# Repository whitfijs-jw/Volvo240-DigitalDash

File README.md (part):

# DigitalDash

Volvo 240 Digital Dash Project.  Designed to use existing dash connectors (circular connectors w/ 2mm pins, vehicle speed sensor (VSS) connector, and various spade connectors) to
minimize extra wiring effort and installation of superfluous sensors.

## Features
### Plug and play with stock sensors and dash connectors
One of the main goals of the project was to use the existing Volvo 240 connectors. The only additional connectors and wiring needed are for sensors that weren't available on the stock main dash (oil pressure, oil temperature, vacuum/boost pressure, etc). Dash lights (low oil pressure, battery voltage, parking brake,high beams, etc) are functional as well as turn indicators. Fuel level and coolant temperature are functional.
The hardware supports the addition of common accessory sensors such as oil pressure, oil temperature, manifold absolute pressure, and ambient temperature.

### Multiple dash styles
Different Volvo dash styles can be displayed:
#### 240 w/ Tach

#### 240 w/ Clock

#### R-Sport Style

#### P1800 Style

#### 850R

#### 740/940 Style

#### 544/140 Linear Style

#### Early 240 Style

#### 140 Rallye Style

#### 240 Style Custom Layouts

### Accessory Gauges
The raspberry pi 4 supports 2 HDMI outputs so a second screen can be added where normal 52mm accessory gauges would have been placed:

Touch screen controls on this screen can be used to changed between dash layouts and also to reset trip odometers.  The style of the accessory gauges reflects the style of the main dash layout.

## Project Structure:
### /QtDash

This directory contains the hardware and software components that makeup the dash. There are also various visual/graphical assets that are used in the dash app.

#### /QtDash/VolvoDigitalDashModels

This directory contains the Qt app and related unit tests.  It is advised to use [QtCreator](https://www.qt.io/product/development-tools) to edit and compile the app. Using QtCreator to `QtDash/VolvoDigitalDashModels/subdirs.pro` will load both the app and the unit tests. The app is written using C/C++ for interfacing with the various sensors and QML for the UI.

#### /QtDash/Hardware

This directory contains the hardware that has been designed for this project.  Most of the PCBs have been designed using Eagle 7.7 as this is what I am most familiar with. The future of Eagle is questionable as an open source/free tool, so Kicad 6 will be used more and more as I become more familiar with it.

##### /QtDash/Hardware/DashHat

This directory contains the schematics and board files for the PCB that directly interfaces with the Raspberry Pi 40 pin header.  The board is split up into a low voltage (3.3/5V) that is powered from the Pi header and a high voltage (car battery voltage 8-16V) that is powered from the 240 ignition switch via the VSS connector.  The high voltage side is optically isolated from the low voltage side using optoislators.

##### /QtDash/Hardware/Cold Start Power Supply

This directory contains the schematics and board files for the cold start tolerant power supply design based around the LM3488. The input range is ~3V-24V and the output is ~5V rated at 3A.  During bench testing the input power needs to be above 5V when first powering up, and then could drop to ~3V while still continuously powering the Pi. This is a little overkill as the battery voltage during cranking only momentarily drops to 3V-4V before recovering very quickly to >10V.

##### /QtDash/Hardware/Screen Mounting

This directory contains the `.stl` files for mounting the HSD123KPW2-D10 12.3" TFT LCD using the stock 240 dash mounting holes.  These mounts will put the screen flush with the surrounding dash. The mounts and all other 3D modeling/CAD has been done using [Onshape](https://cad.onshape.com/documents/a41976d465f773bfdcbe5a50/w/2aee2fa256d8f08e0c531410/e/f563da56c6a88e94f86205e9). Included in the public OnShape document are models of the main PCB, HSD123KPW2-D10 LCD, screen mounts, etc.

##### /QtDash/Hardware/Simulation

This directory contains SPICE simulations of various circuits used in the dash. This is more of a scratchpad than it is a serious attempt at accurate real-life simulations.

##### /QtDash/Hardware/TachAdapter

This directory contains the schematics and board files for the tach signal adapter.  This board takes the high voltage pulses (>30V on my 88 245) and converts them to a square wave that can be used by the dash software to calculate RPM. The high voltage pulses are optically isolated from the dash/pi side to prevent any unwanted noise or damage to the pi or other hardware.

##### /QtDash/Hardware/VSS Adapter

This directory contains the schematics and board files for the VSS signal adapter. This board is based on the MAX9924 VR signal conditioning IC and takes the VR signal from the stock Volvo differential cover sensor and converts it into a square wave to be used by the dash software to calculated speed.

### /buildroot

This directory contains Buildroot, a tool used to generate a custom embedded Linux system that runs on the Pi. Buildroot allows us to generate a stripped down Linux system that has just enough to get the dash running.  This is the directory where you'll need to be to start linux image builds.

Below are relevant directories for this project within the buildroot directory structure:

#### /buildroot/board/volvodash

This directory contains the rootfs overlay for the dash as well as the custom scripts and configurations used whilst building the dash linux image. 

#### /buildroot/configs

This directory contains the configuration files for various boards. The relevant files for this project are `volvodash_defconfig` and `volvodash_rpi4_defconfig`.

#### /buildroot/output/images

This directory contains the outputs of the buildroot compilation process. After buildroot is done compiling the custom linux image, compiling the specified target packages, and constructing the target rootfs and bootfs, an image that can be flashed on to an SD card is placed here.  `sdcard.img` can then be flashed on to an SD card to be used on a pi.  As a part of the compilation/building the Qt Dash app should be compiled and placed within this image.  For more detailed information see *Setting Up Buildroot* below.

## Project components:
- Raspberry Pi 3 or Raspberry Pi 4/400
- 12.3" bar TFT LCD
- Qt Quick w/ EGLFS project to display renders of gauges
- Buildroot linux to cut down on footprint and boot time
- i2c/spi adc interface for reading temp, fuel, speed, etc sensors
- i2c IO expander for warning lights
- Raspberry Pi daughter board to read various sensors.
- DC/DC power supply for screen, pi and sensor supplies, if necessary
- Cheap USB GPS for speedometer and heading (leaving the original speedo behind the dash? Not planning on implementing a validated odometer)

## Current parts (mainly driven by availability):
- HSD123KPW2-D10 12.3" TFT 1920x720 LCD Display w/ HDMI conversion board and custom mounts
- MCP3208 for ADC inputs
- MCP23017SS for dash warning lights and left/right blinkers
- ILQ1 for isolated I/O inputs (3 for 12 inputs) add one more to completely fill the MCP23017
- IL300 for 12V to 3.3V for isolated analog signals (rheostat and battery voltage)
- lM358D for driving IL300 12V isolated analog inputs
- LMV324 & TVS912D for 5V to 3.3V analog sensor inputs
- VK-162 USB GPS module -- needs to be manually configured with u-blox u-center to get 10Hz update rate.
- (optional and separate) LM3488 switching power supply to maintain 5.1V out from 3V-24V input
- (optional) MAX9924 VSS conditioning circuit
- (separate) optocoupler tach pulse input.

## Accessory Screen Parts (optional)
- Adafruit TFP401 HDMI/DVI Decoder to 40-Pin TTL Breakout - With Touch
- BuyDisplay.com 5" IPS 800x480 LCD Screen TFT w/ touch module ER-TFT050-6-5781-4859
- extended 40-pin flat cable
- USB cable for touch screen interface

## Setting up buildroot

Buildroot will build the custom linux image.  The image being build is based on the raspberry-piX 32-bit images provided from the buildroot project.  Right now there is only support for raspberry pi 3 and pi 4/400.  Things are still a bit of a mess here and depending on your flavor of Linux you might have to setup your system a little differently than others.  You can find a lot of good information here on host packages that are absolutely necessary: [Buildroot System Requirements](https://buildroot.org/downloads/manual/manual.html#requirement)

Detailed instructions for setting up a virtual machine and the build environment are found [here](SetupBuildEnv.md)

## Remote Access

1. SSH (ethernet)

After boot the pi will be configured with a static ip address of 192.168.42.2.
Assuming you're running a version of linux that has network-manager you can run some variation of the following after connecting the pi to your computer with an ethernet cable:

`nmcli con add con-name dash-target type ethernet ifname <your-ethernet-interface> ip4 192.168.42.1/24`

`nmcli con up id dash-target`

You can find your ethernet interface by running:

`ip addr show`

You're looking for something like `enp2s0` or `eth0` depending on your flavor of linux.

After setting everything up you can test the connection using:

`ping 192.168.42.2` 

on the host machine and then run:

`ssh root@192.168.42.2` 

and enter the default credentials

## Dash Configuration

After linux is done booting and loading kernel modules, the init system will automatically start the Qt app stored in the /opt directory.  When the app is initializing it will load two configuration files from the /opt directory:

- config.ini
- config_gauges.ini
- config_odo.ini
- config_can.ini

These files are parsed using QSettings ([more info here](https://doc.qt.io/qt-5/qsettings.html)).

### Sensor input configuration (config.ini)

The sensor configuration file contains the configuration for the analog sensor inputs, dash light inputs, user inputs, tach inputs, vss inputs, the isolated 12V inputs, and backlight PWM control.

#### Sensor channels

Under the **[sensor_channel]** section the following inputs can be configured:

| Parameter | Description |
|---|---|
| *coolant_temp* | Stock Volvo coolant temperature sensor/sender. |
| *fuel_level* | Stock Volvo Fuel Level sender |
| *oil_pressure* | Oil Pressure sender |
| *oil_temp* | Oil temperature sender |
| *map_sensor* | MAP sensor sensor (GM 0-5V) |
| *ambient_temp* | Ambient Temperature sender (any NTC sensor can be used) |
| *dimmer_voltage* | Dimmer Rheostat output voltage |
| *fuse8_12v* | Volvo Fuse 8 to measure battery voltage |
| *reference* | A channel configured to measure the unregulated pi 5V supply to decrease measurment error.  If this is not used it is assumed that the supply is exactly 5V. You can alternatively measure your 5V power rail and provide that in the configurations below.|
| *v_supply* | Optional value to set the exact value of the 5V supply.  If left empty exactly 5.0V will be used |

The default configuration is as follows:
```
[sensor_channels]
coolant_temp=0
fuel_level=1
oil_pressure=2
oil_temp=3
map_sensor=5
ambient_temp=4
dimmer_voltage=6
fuse8_12v=7
reference=-1
v_supply=5.1
```

#### Dash Light Inputs

Under the **[dash_lights]** section the following inputs can be configured:

| Parameter | Description |
|---|---|
| *oil_pressure_sw* | Stock oil pressure switch |
| *od_lamp* | Overdrive lamp |
| *high_beam* | High beam indication |
| *brake_failure* | brake failure indication |
| *bulb_failure* | bulb failure indication |
| *charging* | Alternator D+/Battery charge failure indication |
| *blinker_left* | Left blinker indication |
| *blinker_right* | Right blinker indication |
| *od_lamp_auto* | auto trans OD lamp |
| *check_engine* | Check Engine indication |
| *parking_brake* | Parking Brake engagement indication |
| *conn_32_pin3* | Half moon connector pin 3 (ABS light in newer 240s) |

and one additional option:

- *active_low* -- Optoisolator outputs are open collector so this should be set to 1 unless changes to the hardware have been made

The default configuration is as follows:

```
[dash_lights]
active_low=1
oil_pressure_sw=0
od_lamp=1
high_beam=2
brake_failure=3
bulb_failure=7
charging=6
blinker_left=5
blinker_right=4
od_lamp_auto=8
check_engine=9
parking_brake=10
conn_32_pin3=11
```
#### User Input configuration

There are 4 user inputs in Rev C and greater hardware.  They are active low inputs on the otherwise unused pins on the MCP23017.

Under the **[user_inputs]** section the following inputs can be configured:

| Parameter | Description |
|---|---|
| *input_1* | User input 1 pin number |
| *input_2* | User input 2 pin number |
| *input_3* | User input 3 pin number |
| *input_4* | User input 4 pin number |
| *input_1_map* | User input 1 key mapping |
| *input_2_map* | User input 2 key mapping |
| *input_3_map* | User input 3 key mapping |
| *input_4_map* | User input 4 key mapping |

The default configuration is as follows:

```
[user_inputs]
input_1=12
input_2=13
input_3=14
input_4=15
input_1_map="Key_Left"
input_2_map="Key_A"
input_3_map="Key_B"
input_4_map="Key_Right"
```

Available key mappings are:
```
"Key_Left"
"Key_Right"
"Key_Up"
"Key_Down"
"Key_A"
"Key_B"
"Key_C"
"Key_D"
"Key_1"
"Key_2"
"Key_3"
"Key_4"
```

"Key_Left" and "Key_Right" are used to change dash layouts.  Other keys will be mapped to other functions in the future (resetting trip counters, for example).

#### MAP Sensor configuration

Designed for a GM style 0-5V output MAP sensor (1 bar, 2 bar, 3 bar). Under the **[map_sensor]** section the following parameters can be configured:

| Parameter | Description |
|---|---|
| *p_0v* | pressure when sensor output is 0V |
| *p_5v* | pressure when sensor output is 5V |
| *p_atm* | atmospheric pressure |
| *units* | pressure units used for above values.  "kPa", "psi" or "bar" should be used |

The default configuration is for a 3 bar GM style map sensor:

```
[map_sensor]
p_0v=3.6
p_5v=315
units="kPa"
```

#### Temperature Sensor (NTC) Configuration

An array of NTC sensor configurations. Calibration curves are calculated using the [Steinhart-Hart equation](https://en.wikipedia.org/wiki/Steinhart%E2%80%93Hart_equation). Under the **[temp_sensor]** the following parameters can be configured:

| Parameter | Description |
|---|---|
| *type* | Sensor type.  Options are "coolant", "oil", and "ambient" |
| *r_balance* | Resistance of the balance resistor. This can be calculated based on the high and low resistances expected during operation. |
| *t1_temp* 	|  Temperature at first calibration point |
| *t1_R* 		| Resistance at first calibration point |
| *t2_temp* 	| Temperature at second calibration point |
| *t2_R* 		| Resistance at second calibration point |
| *t3_temp* 	| Temperature at third calibration point |
| *t3_R* 		| Resistance at third valibration point |
| units | Temperature units used.  Options are "C", "K", "F" |

The default configuration is designed for an early type stock 240 coolant temp sensor, a VDO 325-905 Oil temperature sender, and a random ambient temp sensor for a BMW off Amazon.

```
[temp_sensor]
size=3
[temp_sensor/1]
type="coolant"
r_balance=470
t1_temp=60
t1_R=217
t2_temp=90
t2_R=87
t3_temp=100
t3_R=67
units="C"
[temp_sensor/2]
type="oil"
r_balance=150.0
t1_temp=19.5
t1_R=1325
t2_temp=100
t2_R=78.5
t3_temp=157
t3_R=40.5
units="C"
[temp_sensor/3]
type="ambient"
r_balance=6490
t1_temp=1.0
t1_R=15800
t2_temp=20
t2_R=6400
t3_temp=36
t3_R=3360
units="C"
```

#### Resistive Sensor Configuration

An array of resistive sensor configurations. Calibration values can be interpolated (not advised unless a lot of data points are available) or can be fitted with a polynomial of an arbitray order.  Usually a 2nd order polynomial is good enough.  The following parameters can be configured:

| Parameter | Description |
|---|---|
| *type* | Sensor type.  Options are "coolant", "oil", and "ambient" |
| *fit* | Type of fit. Options are "interpolate" or "polynomial, N" with N as the polynomial order.
| *r_balance* | Resistance of the balance resistor. This can be calculated based on the high and low resistances expected during operation. |
| *r* | Calibration resistance values.|
| *y* | Calibration y values |
| *units* | Units of calibration y values |
| *lag* | Lag factor (0-1).  Used to filter values with the difference equation: **y[n] = lag \* x[n] + (1 - lag) \* y[n-1]** Default value is 1.0. |
|*lag_decay*| Lag decay factor.  If set to a non-zero value the following equation will dictate the lag factor value used above: **lagStart=1-*lag*, lag[n] = lagStart \* (1 - *lag_decay*)^(n)** and saturates at the value set by *lag*. Large values will decay quickly, small values slowly.  Default value is 0.0.  |

The default configuration is designed for a VDO 360-028 Oil pressure sender and a 240-33Ohm Volvo 240 Fuel level sender.

```
[resistive_sensor]
size=2
[resistive_sensor/1]
type="oil_pressure"
fit=polynomial,2
r_balance=43.0
r=10.0,48.0,82.0,116.0,184.0
y=0.0,1.0,2.0,3.0,5.0
units="bar"
lag=1.0
[resistive_sensor/2]
type="fuel_level"
fit=polynomial,3
r_balance=91.0
r=240,196,153,125,103,87,67,45,33
y=0.0,12.5,25.0,37.5,50.0,62.5,75.0,87.5,100
units="%"
lag=0.2
```

#### Analog 12V inputs.

To measure signals that are inherently tied to battery voltage there are 2 linearized opto-isolated inputs.  The following parameters can be configured:

| Parameter | Description |
|---|---|
| *name* | Sensor name.  "voltmeter" is the only one currently used |
| *opto_r1* | Isolated side (R59 in schematic below) |
| *opto_r2* | Opto-isolator gain resistor R2 (R62 in schematic below) |
| *input_r1* | High side resistor of voltage divider for input into opto-isolator. (R71 in schematic below) |
| *input_r2* | Low side resistor of voltage divivider for input into opto-isolator. (R72 in schematic below) |
| *k3* | Opto-isolator K3 gain (defined by linearized opto-isolator used and will have to be measured) |
| *offset* | Offset to voltage calculation, the linearized opto-isolator usually has an offset that will need to be accounted for. |
| *x* | Linearized opto-isolator input voltage calibration measurements.  This is the high voltage side.  The more measurement points the better.   |
| *y* | Output voltage calibration measurements.  This is the low voltage side.  Ideally if there was zero offset and a K3 gain of 1.0 these should be x / 10.  This is unlikely to be the case given the binning of the IL300 and LOC11x series. |

##### How to determine K3 value (still need to test on car -- likely to change)
1. In the config.ini file, set *opto_r1*, *opto_r2*, *input_r1*, *input_r2*, and *k3* to 1.0.
2. In the config.ini file, set *offset* to 0.0.
3. Reboot the dash.
4. The output for the voltmeters will now be the real input to the ADC. Usually between 1V-2V for inputs from 8V to 16V.
5. With the car on but not running, measure the voltage at fuse 8.  This will be your first x value.  Take the output of the voltmeter (somewhere between 1V-2V).  This will be your first y value.
6. Start the car and repeat the above step.  These will be your second x and y values.
7. Enter the values determined above in the config.ini file.
8. Reset the *opto_r1*, *opto_r2*, *input_r1*, *input_r2* to their previous values.  You can leave *offset* and *k3* alone.  The software will use your calibration values to calculate the k3 gain and offset.
9. Reboot the dash and verify that the voltages with the car on and running match what you had measured before.

*Note on K3 gain calibration values:*
*Ideally, you would want way more than just 2 points to calibrate with.  If you have access to an adjustable power supply it is recommended to take 5+ measurements from 8V-16V.*

The default configuration is as follows:

```
[12v_analog]
size=2
[12v_analog/1]
name="voltmeter"
opto_r1=490000.0
opto_r2=100000.0
input_r1=100000.0
input_r2=100000.0
k3=1.1536
offset=.087985
x=8.25, 9.05, 9.87, 10.67, 11.52, 12.37, 13.30, 14.15, 14.96, 15.78, 16.78
y=1.05, 1.15, 1.25, 1.35, 1.45, 1.55, 1.65, 1.76, 1.85, 1.95, 2.05
[12v_analog/2]
name="rheostat"
opto_r1=490000.0
opto_r2=100000.0
input_r1=100000.0
input_r2=100000.0
k3=1.1536
offset=.087985
x=8.25, 9.05, 9.87, 10.67, 11.52, 12.37, 13.30, 14.15, 14.96, 15.78, 16.78
y=1.05, 1.15, 1.25, 1.35, 1.45, 1.55, 1.65, 1.76, 1.85, 1.95, 2.05
```

#### Tach Input Configuration

RPM is estimated by measuring the time difference between pulses from the negative terminal of the ignition coil.  The following parameters can be configured:

| Parameter | Description |
|---|---|
| *pulse_per_rot* | Number of tach pulses per rotation (number of cylinders / 2) |
| *max_rpm* | Maximum RPM to resolve.  This should be as low as possible. |
| *avg_num_samples* | Number of samples to average over to estimate RPM |

The default configuration is as follows:

```
[tach_input]
pulse_per_rot=2
max_rpm=9000
avg_num_samples=4
```

#### Vehicle speed sensor input

Designed to used the stock 240 diff cover VSS. The vehicle speed can be estimated using the number of pulses coming from the VSS sensor for every rotation of the rear diff. The following parameters can be configured:

| Parameter | Description |
|---|---|
| *pulse_per_rot* | Number of VSS pulses per rotation (12 for non-ABS and 48 for ABS equipped 240s) |
| *tire_diameter* | Tire diameter (can be used to calculate pulses per unit distance) |
| *diameter_units* | Tire diameter units: "inch", "centimeter", "millimeter", "foot", etc  |
| *pulse_per_unit_distance* | Number of pulses per units distance.   |
| *distance_units* | Distance units for pulses per unit distance:  "mile", "kilometer  |
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
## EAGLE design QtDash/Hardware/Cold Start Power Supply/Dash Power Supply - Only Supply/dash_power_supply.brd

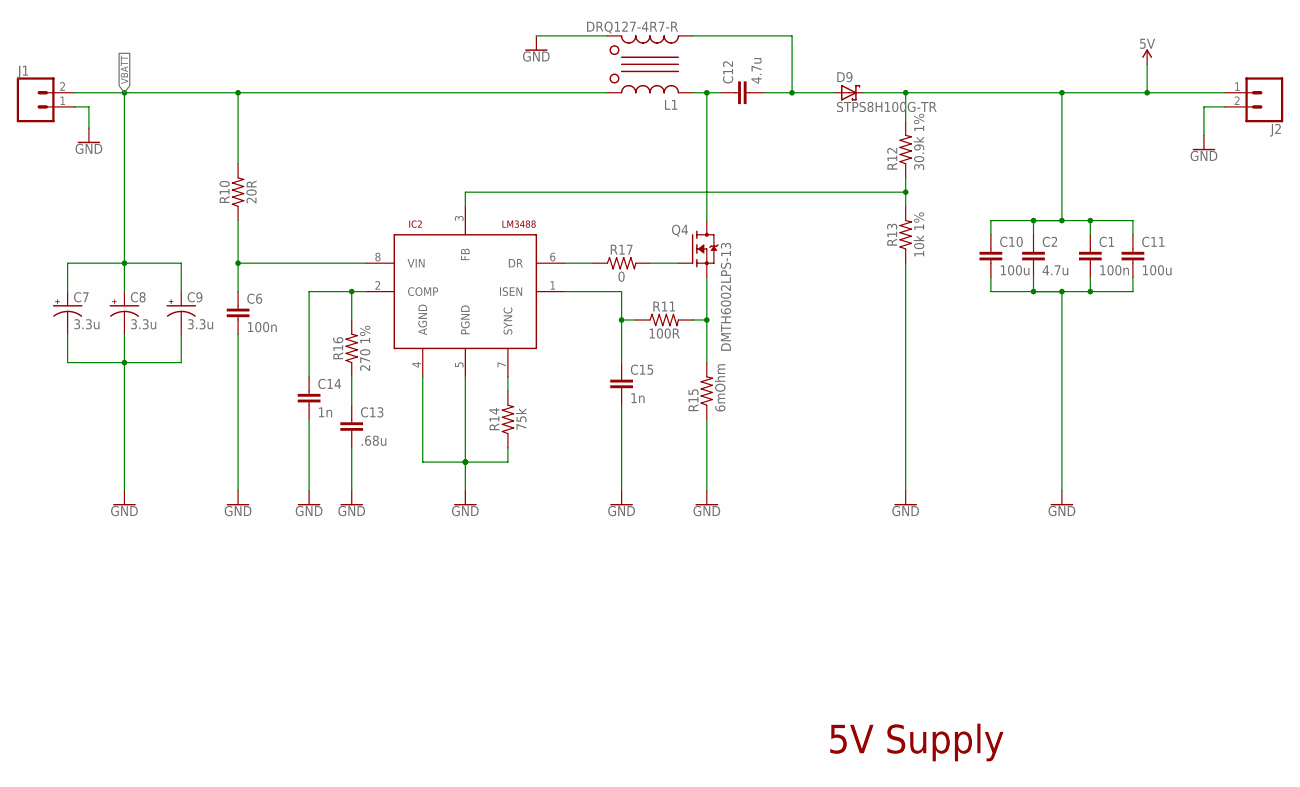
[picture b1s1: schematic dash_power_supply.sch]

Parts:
C1, C6: 100n; 0603
C2, C12: 4.7u; 0603
C7, C8, C9: 3.3u; PANASONIC_C
C10, C11: 100u; C1210
C13: .68u; 0603
C14, C15: 1n; 0603
D9: STPS8H100G-TR; TO263
IC2: LM3488; VSSOP-8
J1, J2: CONN_02PTH4; 1X02_XTRA_BIG
L1: DRQ127-4R7-R; DRQ127
Q4: DMTH6002LPS-13; TDSON
R10: 20R; 0603
R11: 100R; 0603
R12: 30.9k 1%; R1206
R13: 10k 1%; 0603
R14: 75k; 0603
R15: 6mOhm; 3216
R16: 270 1%; 0603
R17: 0; 0603

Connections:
5V: C1.1, C2.1, C10.1, C11.1, D9.3 (C), J2.1, R12.2
GND: C1.2, C2.2, C6.2, C7.-, C8.-, C9.-, C10.2, C11.2, C13.2, C14.2, C15.2, IC2.4 (AGND), IC2.5 (PGND), J1.1, J2.2, L1.2, R13.1, R14.1, R15.1
unnamed: Q4.4 (G), R17.2
unnamed: C6.1, IC2.8 (VIN), R10.1
unnamed: IC2.3 (FB), R12.1, R13.2
unnamed: IC2.6 (DR), R17.1
unnamed: C15.1, IC2.1 (ISEN), R11.1
unnamed: Q4.1 (S), Q4.2 (S), Q4.3 (S), R11.2, R15.2
unnamed: C12.1, L1.3, Q4.5 (D)
unnamed: C12.2, D9.2 (A), L1.4
unnamed: C14.1, IC2.2 (COMP), R16.2
unnamed: C13.1, R16.1
unnamed: IC2.7 (SYNC), R14.2
VBATT: C7.+, C8.+, C9.+, J1.2, L1.1, R10.2

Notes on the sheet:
5V Supply

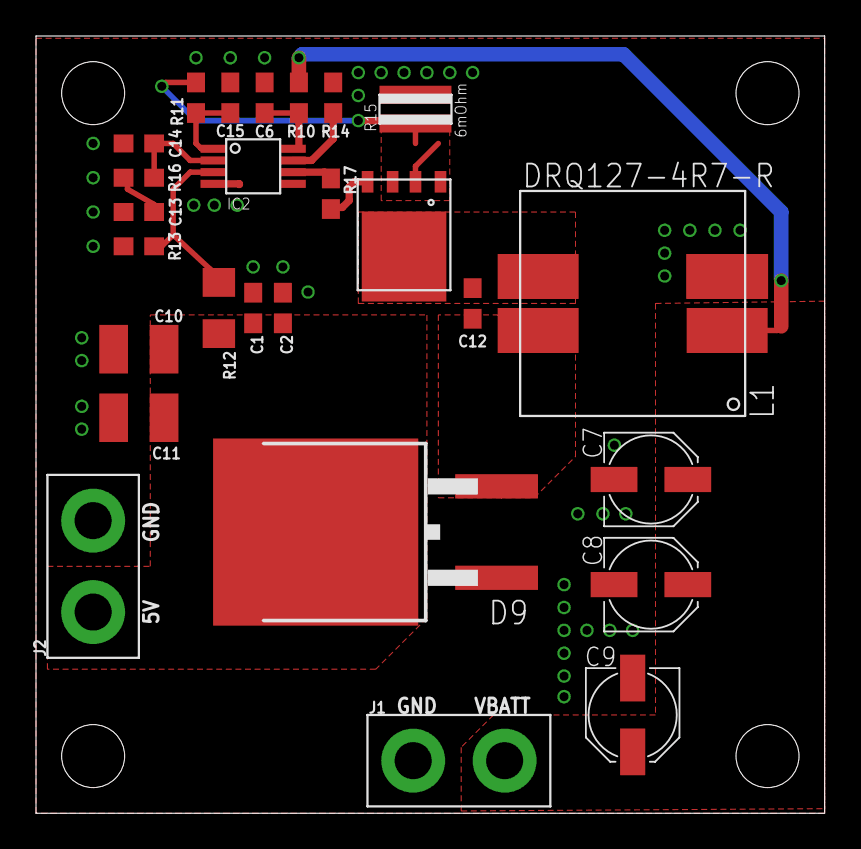
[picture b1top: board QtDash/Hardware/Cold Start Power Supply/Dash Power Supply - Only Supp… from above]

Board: 2 copper layers, 43.8 x 43.2 mm, 26 parts (0 on the bottom side), 14 nets.

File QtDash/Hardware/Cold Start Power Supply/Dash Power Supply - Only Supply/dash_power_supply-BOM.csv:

"Part";"Value";"Device";"Package";"Description";"POWER";"PROD_ID";"VALUE";"VOLTAGE";
"C1";"100n";"CL10B104MB8NNNC";"0603";"";"";"";"100n";"50V";
"C2";"4.7u";"CL10A475KL8NRNC";"0603";"";"";"";"4.7u";"35V";
"C6";"100n";"CL10B104MB8NNNC";"0603";"";"";"";"100n";"50V";
"C7";"3.3u";"EEV-FK1K3R3R";"PANASONIC_C";"";"";"";"3.3u";"80v";
"C8";"3.3u";"EEV-FK1K3R3R";"PANASONIC_C";"";"";"";"3.3u";"80v";
"C9";"3.3u";"EEV-FK1K3R3R";"PANASONIC_C";"";"";"";"3.3u";"80v";
"C10";"100u";"CL32A107MPVNNNE";"C1210";"";"";"";"100u";"10V";
"C11";"100u";"CL32A107MPVNNNE";"C1210";"";"";"";"100u";"10V";
"C12";"4.7u";"CL10A475KL8NRNC";"0603";"";"";"";"4.7u";"35V";
"C13";".68u";"CL10B684KO8NFNC";"0603";"";"";"";".68u";"16V";
"C14";"1n";"CL10B102KB8NNWC";"0603";"";"";"";"1n";"50V";
"C15";"1n";"CL10B102KB8NNWC";"0603";"";"";"";"1n";"50V";
"D9";"STPS8H100G-TR";"STPS8H100G-TR";"TO263";"";"";"";"";"";
"IC2";"LM3488";"LM3488";"VSSOP-8";"";"";"";"";"";
"J1";"";"CONN_02PTH4";"1X02_XTRA_BIG";"Multi connection point. Often used as Generic Header-pin footprint for 0.1 inch spaced/style header connections";"";"";"";"";
"J2";"";"CONN_02PTH4";"1X02_XTRA_BIG";"Multi connection point. Often used as Generic Header-pin footprint for 0.1 inch spaced/style header connections";"";"";"";"";
"L1";"DRQ127-4R7-R";"DRQ127-4R7-R";"DRQ127";"";"";"";"";"";
"Q4";"DMTH6002LPS-13";"DMTH6002LPS-13";"TDSON";"";"";"";"";"";
"R10";"20R";"RC0603JR-0720RL";"0603";"";"";"";"20R";"";
"R11";"100R";"RC0603JR-07100RL";"0603";"";"";"";"100R";"";
"R12";"30.9k 1%";"RC1206FR-0730K9L";"R1206";"";".25W";"";"30.9k 1%";"";
"R13";"10k 1%";"RC0603FR-1010KL";"0603";"";"";"";"10k 1%";"";
"R14";"75k";"75KOHM-0603-1/10W-1%";"0603";"75kΩ resistor";"";"RES-09737";"75k";"";
"R15";"6mOhm";"PRL1632-R006-F-T1";"3216";"";"1W";"";"6mOhm";"";
"R16";"270 1%";"RC0603FR-07270RL";"0603";"";"";"";"270 1%";"";
"R17";"0";"0OHM-0603-1/10W";"0603";"0Ω resistor";"";"RES-08609";"0";"";

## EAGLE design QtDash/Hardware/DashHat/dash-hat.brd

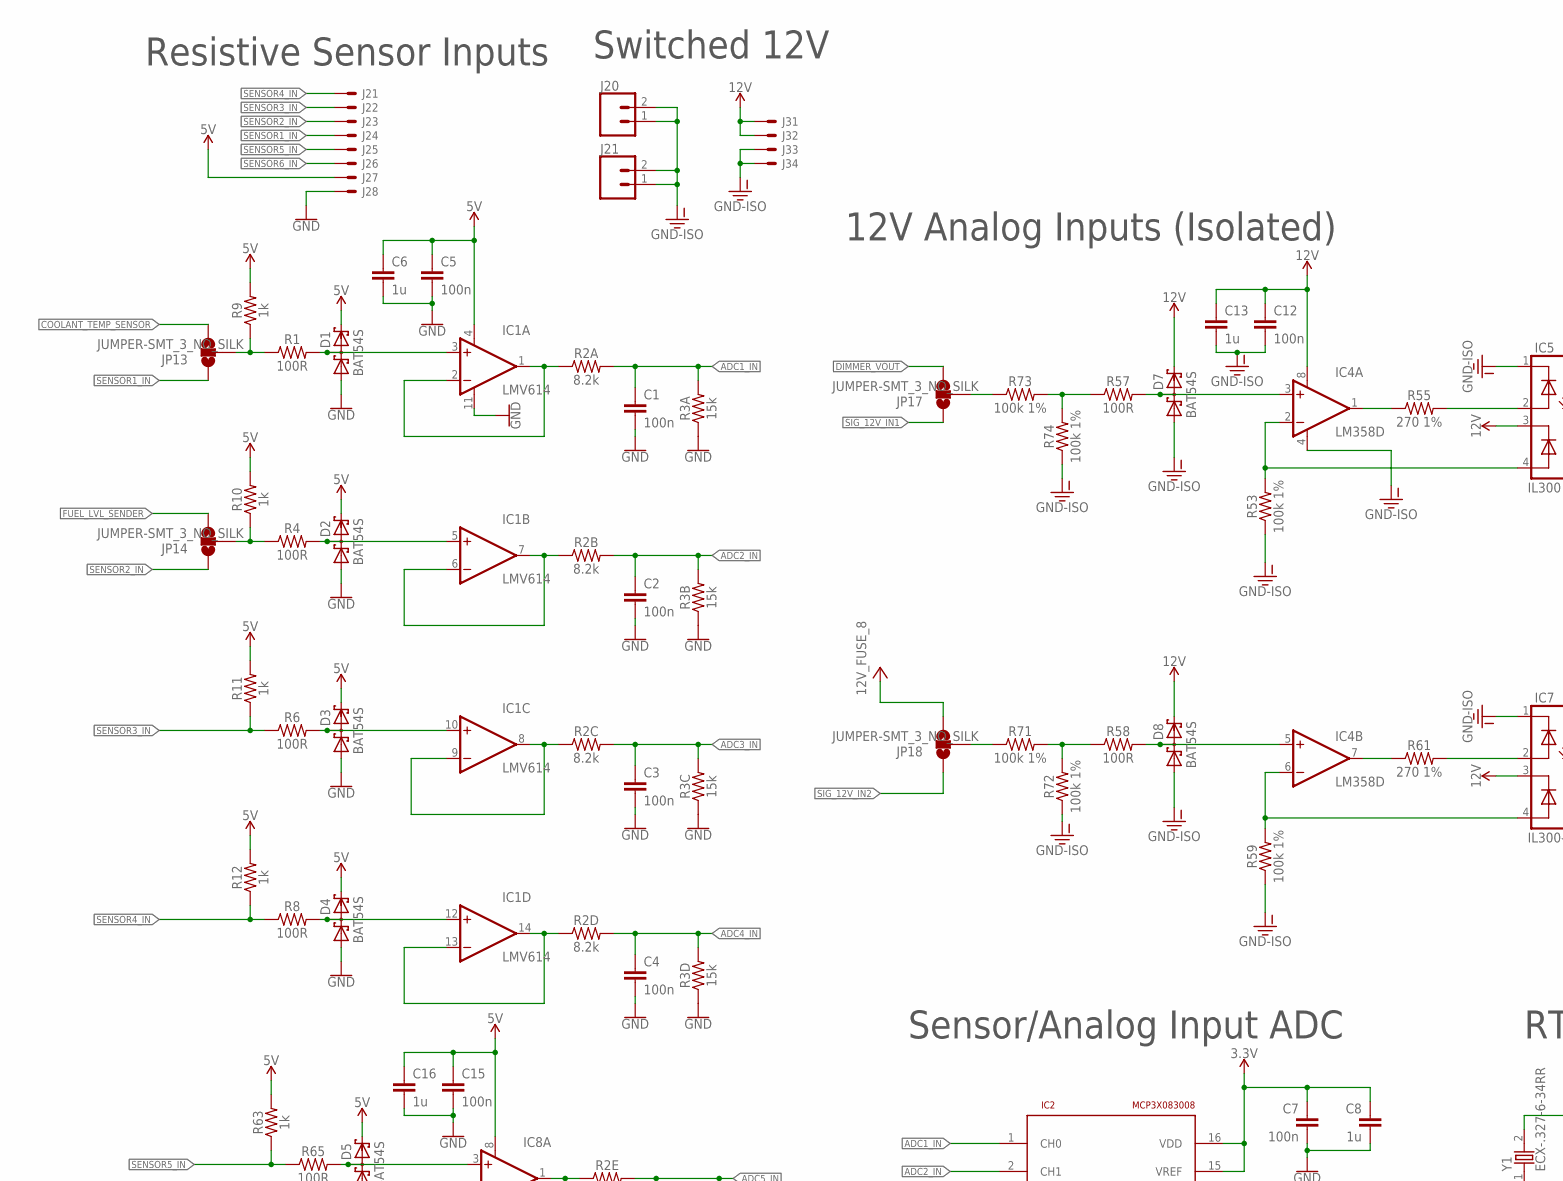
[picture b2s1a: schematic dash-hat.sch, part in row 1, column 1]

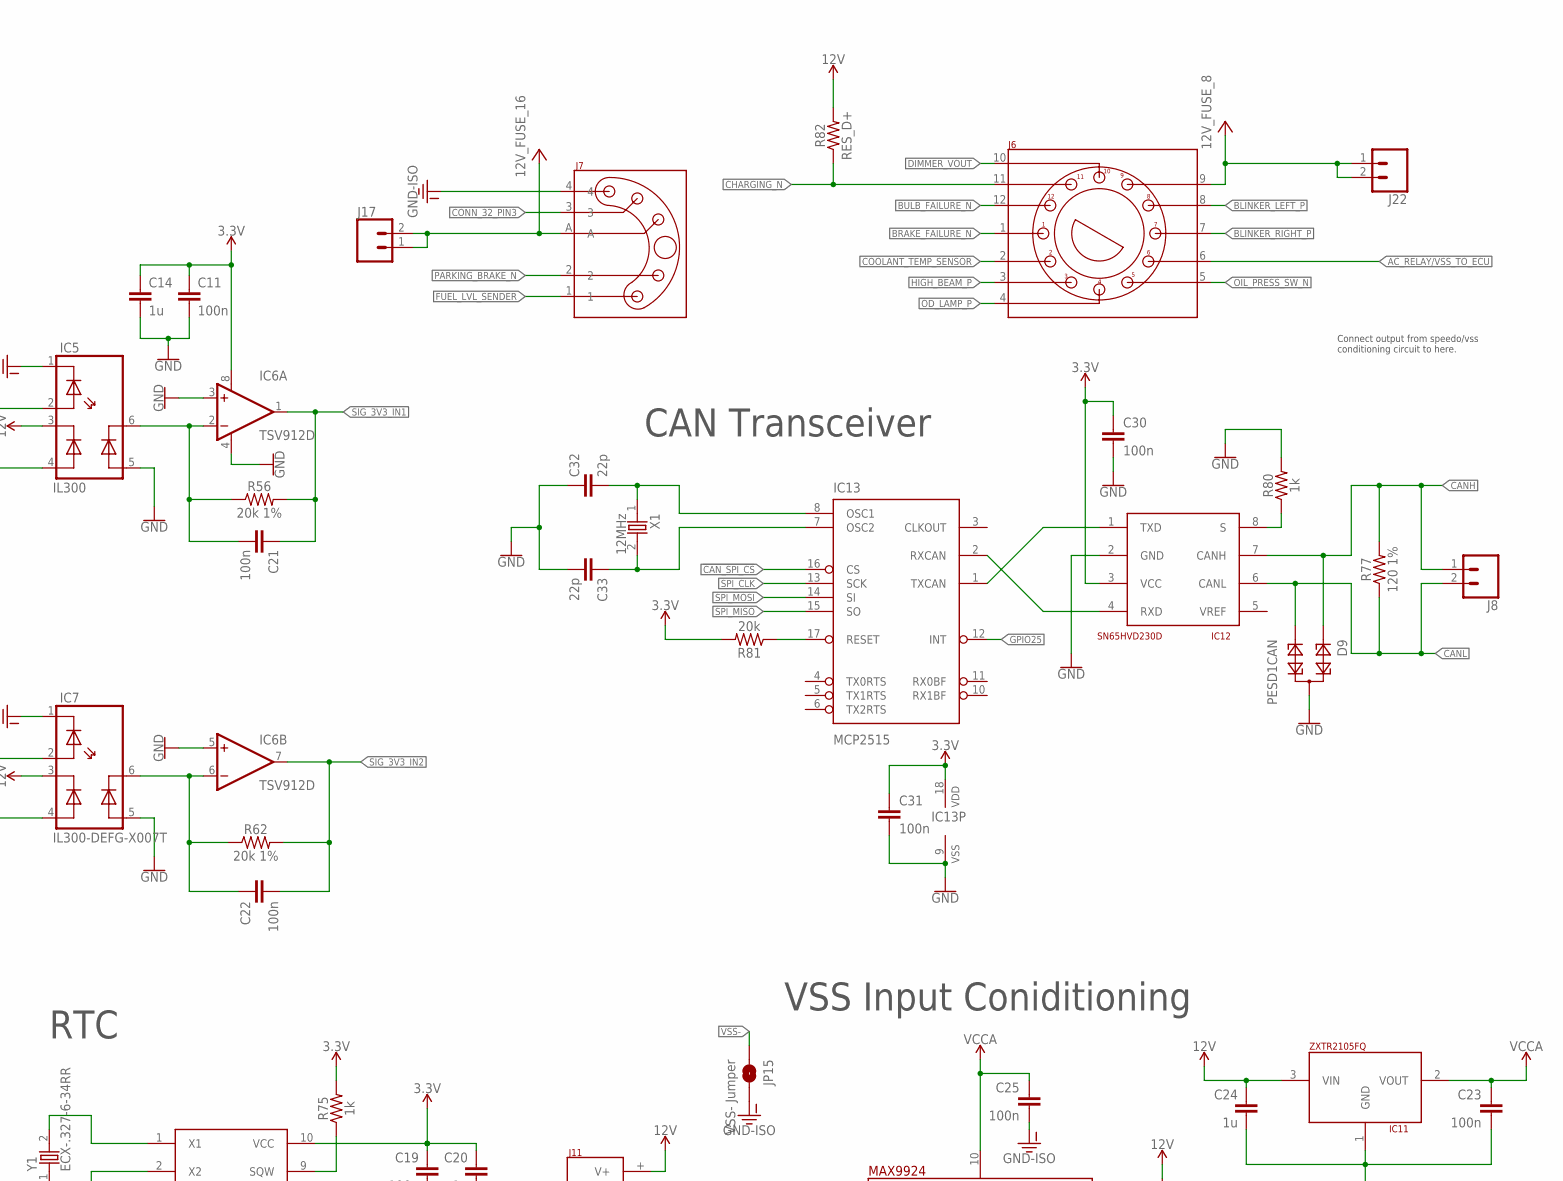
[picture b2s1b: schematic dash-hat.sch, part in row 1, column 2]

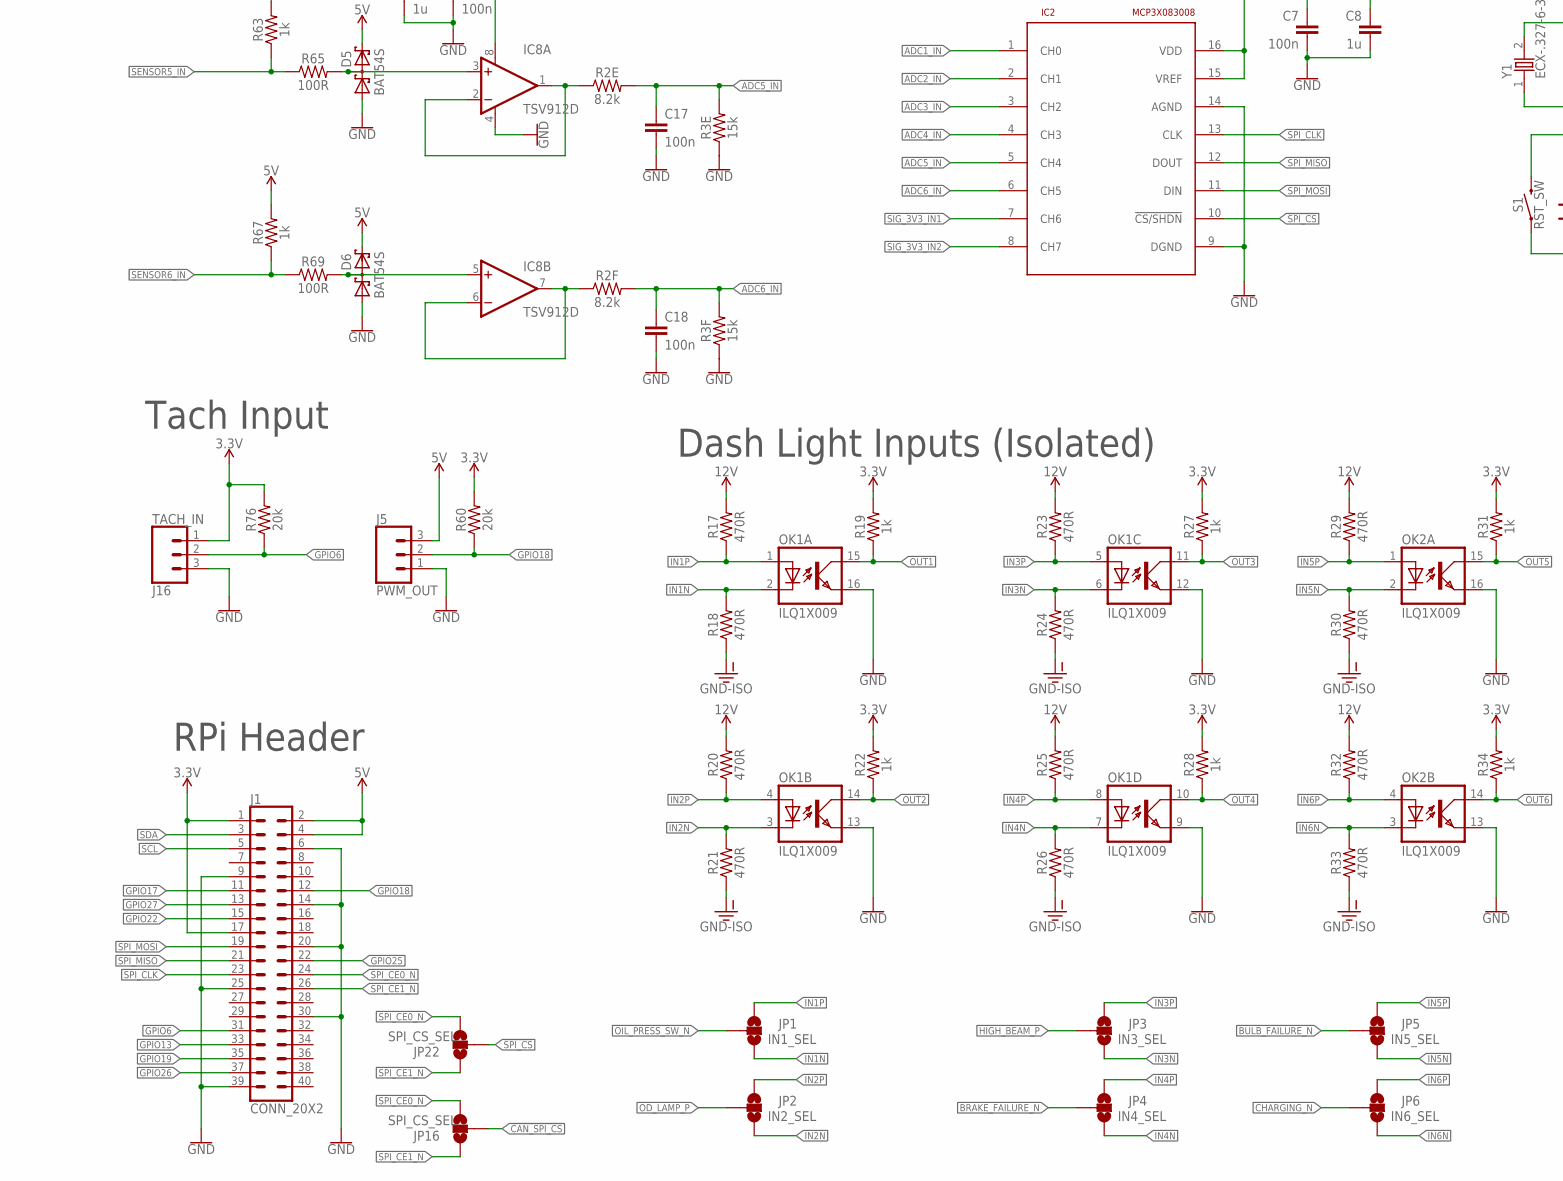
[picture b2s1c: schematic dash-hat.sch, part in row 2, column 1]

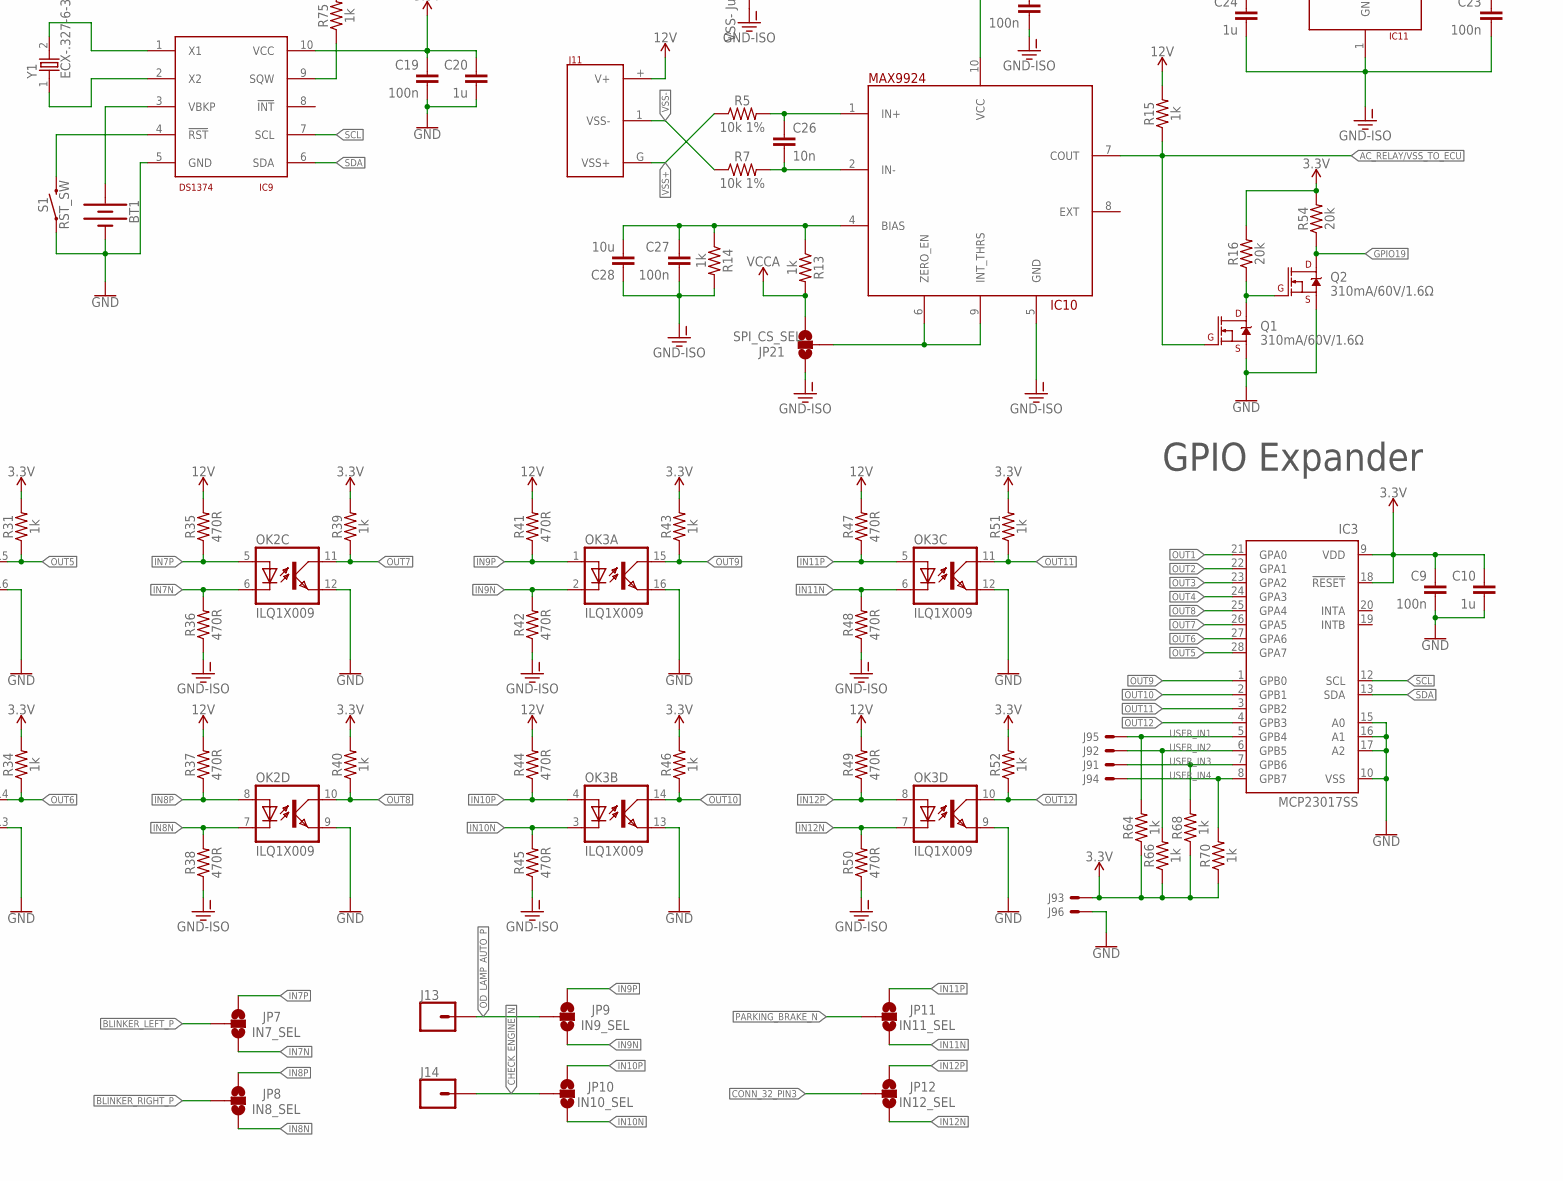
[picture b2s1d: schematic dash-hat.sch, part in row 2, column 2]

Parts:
BT1: BATTERY-12MM_SMD; BATTCON_12MM
C1, C2, C3, C4, C5, C7, C9, C11, C12, C15, C17, C18, C19, C21, C22, C23, C25, C27, C30, C31: 100n; 0603
C6, C8, C10, C13, C14, C16, C20, C24: 1u; 0603
C26: 10n; 0603
C28: 10u; 0603
C32, C33: 22p; 0603
D1, D2, D3, D4, D5, D6, D7, D8: BAT54S; SOT23
D9: PESD1CAN; SOT23
IC1: LMV614; TSSOP14
IC2: MCP3X083008; SO16
IC3: MCP23017SS; SSOP28
IC4: LM358D; SO08
IC5: IL300; DIL8-SMD
IC6, IC8: TSV912D; SO08
IC7: IL300-DEFG-X007T; DIL8-SMD
IC9: DS1374; UMAX10
IC10: MAX9924; UMAX10
IC11: ZXTR2105FQ; SOT23
IC12: SN65HVD230D; SO08
IC13: MCP2515; SO18W
J1: CONN_20X2; 2X20
J2: CONN_04X2; MOLEX-1053102108
J3: CONN_04RIGHT-ANGLE; MOLEX-1053141204
J5: PWM_OUT; 1X03_JST-XHP
J6: VOLVO_CONN_31; VOLVO_CON_31
J7: VOLVO_CONN_32; VOLVO_CON_32
J8: CONN_02JST-XHP; 1X02_JST-XHP
J9: CONN_03X2; MOLEX-1053101106
J11: VOLVO_CONN_VSS
J13, J14: CONN_01PTH_2MM; 1X01_2MM
J16: TACH_IN; 1X03_JST-XHP
J17, J20, J21, J22: CONN_02PTH4; 1X02_XTRA_BIG
JP1: IN1_SEL; SMT-JUMPER_3_NO_SILK
JP2: IN2_SEL; SMT-JUMPER_3_NO_SILK
JP3: IN3_SEL; SMT-JUMPER_3_NO_SILK
JP4: IN4_SEL; SMT-JUMPER_3_NO_SILK
JP5: IN5_SEL; SMT-JUMPER_3_NO_SILK
JP6: IN6_SEL; SMT-JUMPER_3_NO_SILK
JP7: IN7_SEL; SMT-JUMPER_3_NO_SILK
JP8: IN8_SEL; SMT-JUMPER_3_NO_SILK
JP9: IN9_SEL; SMT-JUMPER_3_NO_SILK
JP10: IN10_SEL; SMT-JUMPER_3_NO_SILK
JP11: IN11_SEL; SMT-JUMPER_3_NO_SILK
JP12: IN12_SEL; SMT-JUMPER_3_NO_SILK
JP13, JP14, JP17, JP18: JUMPER-SMT_3_NO_SILK; SMT-JUMPER_3_NO_SILK
JP15: VSS- Jumper; SMT-JUMPER_2_NO_SILK
JP16, JP21, JP22: SPI_CS_SEL; SMT-JUMPER_3_NO_SILK
OK1, OK2, OK3: ILQ1X009; SMD16
Q1, Q2: 310mA/60V/1.6Ω; SOT323
R1, R4, R6, R8, R57, R58, R65, R69: 100R; 0603
R2: 8.2k; YC248
R3: 15k; YC248
R5, R7: 10k 1%; 0603
R9, R10, R11, R12, R13, R14, R15, R19, R22, R27, R28, R31, R34, R39, R40, R43, R46, R51, R52, R63, R64, R66, R67, R68, R70, R75, R80: 1k; 0603
R16, R54, R60, R76, R81: 20k; 0603
R17, R18, R20, R21, R23, R24, R25, R26, R29, R30, R32, R33, R35, R36, R37, R38, R41, R42, R44, R45, R47, R48, R49, R50: 470R; 0603
R53, R59, R71, R72, R73, R74: 100k 1%; 0603
R55, R61: 270 1%; 0603
R56, R62: 20k 1%; 0603
R77: 120 1%; 0603
R82: RES_D+; 0617/17
S1: RST_SW; TACTILE_SWITCH_SMD_6.0X3.5MM
X1: 12MHz; ECS
Y1: ECX-.327-6-34RR; ECX-34RR

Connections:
3.3V: C7.1, C8.1, C9.1, C10.1, C11.1, C14.1, C19.1, C20.1, C30.1, C31.1, IC2.15 (VREF), IC2.16 (VDD), IC3.9 (VDD), IC3.18 (!RESET), IC6.8 (V+), IC9.10 (VCC), IC12.3 (VCC), IC13.18 (VDD), J1.1, J1.17, J9.3, J16.1, R16.2, R19.2, R22.2, R27.2, R28.2, R31.2, R34.2, R39.2, R40.2, R43.2, R46.2, R51.2, R52.2, R54.2, R60.2, R64.1, R66.1, R68.1, R70.1, R75.2, R76.2, R81.2
5V: C5.1, C6.1, C15.1, C16.1, D1.2 (C2), D2.2 (C2), D3.2 (C2), D4.2 (C2), D5.2 (C2), D6.2 (C2), IC1.4 (V+), IC8.8 (V+), J1.2, J1.4, J2.7, J5.3, R9.2, R10.2, R11.2, R12.2, R63.2, R67.2
12V: C12.1, C13.1, C24.1, D7.2 (C2), D8.2 (C2), IC4.8 (V+), IC5.3 (C3), IC7.3 (C3), IC11.3 (VIN), J3.1, J3.2, J11.+ (V+), R15.2, R17.2, R20.2, R23.2, R25.2, R29.2, R32.2, R35.2, R37.2, R41.2, R44.2, R47.2, R49.2, R82.2
12V-FUSE_8: J6.9, J22.1, J22.2, JP18.3
12V-FUSE_16: J7.A, J17.1, J17.2
!CAN_SPI_CS: IC13.16 (CS), JP16.2
!SPI_CS: IC2.10 (!CS/SHDN), JP22.2
AC_RELAY/VSS_TO_ECU: IC10.7 (COUT), J6.6, Q1.1 (G), R15.1
ADC1_IN: C1.1, IC2.1 (CH0), R2.16 (2), R3.16 (2)
ADC2_IN: C2.1, IC2.2 (CH1), R2.15 (2), R3.15 (2)
ADC3_IN: C3.1, IC2.3 (CH2), R2.14 (2), R3.14 (2)
ADC4_IN: C4.1, IC2.4 (CH3), R2.13 (2), R3.13 (2)
ADC5_IN: C17.1, IC2.5 (CH4), R2.12 (2), R3.12 (2)
ADC6_IN: C18.1, IC2.6 (CH5), R2.11 (2), R3.11 (2)
BLINKER_LEFT_P: J6.8, JP7.2
BLINKER_RIGHT_P: J6.7, JP8.2
BRAKE_FAILURE_N: J6.1, JP4.2
BULB_FAILURE_N: J6.12, JP5.2
CANH: D9.1, IC12.7 (CANH), J8.1, R77.2
CANL: D9.2, IC12.6 (CANL), J8.2, R77.1
CHARGING_N: J6.11, JP6.2, R82.1
CHECK_ENGINE_N: J14.1, JP10.2
CONN_32_PIN3: J7.3, JP12.2
COOLANT_TEMP_SENSOR: J6.2, JP13.3
DIMMER_VOUT: J6.10, JP17.3
FUEL_LVL_SENDER: J7.1, JP14.3
GND: BT1.GND (-), C1.2, C2.2, C3.2, C4.2, C5.2, C6.2, C7.2, C8.2, C9.2, C10.2, C11.2, C14.2, C15.2, C16.2, C17.2, C18.2, C19.2, C20.2, C30.2, C31.2, C32.1, C33.2, D1.1 (A1), D2.1 (A1), D3.1 (A1), D4.1 (A1), D5.1 (A1), D6.1 (A1), D9.3, IC1.11 (V-), IC2.9 (DGND), IC2.14 (AGND), IC3.10 (VSS), IC3.15 (A0), IC3.16 (A1), IC3.17 (A2), IC5.5 (A5), IC6.3 (+IN), IC6.4 (V-), IC6.5 (+IN), IC7.5 (A5), IC8.4 (V-), IC9.5 (GND), IC12.2 (GND), IC13.9 (VSS), J1.6, J1.9, J1.14, J1.20, J1.25, J1.30, J1.39, J2.8, J5.1, J9.6, J16.3, OK1.9 (EMIT), OK1.12 (EMIT), OK1.13 (EMIT), OK1.16 (EMIT), OK2.9 (EMIT), OK2.12 (EMIT), OK2.13 (EMIT), OK2.16 (EMIT), OK3.9 (EMIT), OK3.12 (EMIT), OK3.13 (EMIT), OK3.16 (EMIT), Q1.2 (S), Q2.2 (S), R3.1, R3.2 (1), R3.3 (1), R3.4 (1), R3.5 (1), R3.6 (1), R80.2, S1.1
GND-ISO: C12.2, C13.2, C23.2, C24.2, C25.2, C27.2, C28.1, D7.1 (A1), D8.1 (A1), IC4.4 (V-), IC5.1 (C1), IC7.1 (C1), IC10.5 (GND), IC11.1 (GND), J3.3, J3.4, J7.4, J20.1, J20.2, J21.1, J21.2, JP15.2, JP21.1, R14.2, R18.1, R21.1, R24.1, R26.1, R30.1, R33.1, R36.1, R38.1, R42.1, R45.1, R48.1, R50.1, R53.1, R59.1, R72.1, R74.1
GPIO6: J1.31, J16.2, R76.1
GPIO13: J1.33
GPIO17: J1.11
GPIO18: J1.12, J5.2, R60.1
GPIO19: J1.35, Q2.3 (D), R54.1
GPIO22: J1.15
GPIO25: IC13.12 (INT), J1.22
GPIO26: J1.37
GPIO27: J1.13
HIGH_BEAM_P: J6.3, JP3.2
IN1N: JP1.3, OK1.2 (C), R18.2
IN1P: JP1.1, OK1.1 (A), R17.1
IN1_12V_SIGNAL: R57.1, R73.2, R74.2
IN2N: JP2.3, OK1.3 (C), R21.2
IN2P: JP2.1, OK1.4 (A), R20.1
IN3N: JP3.3, OK1.6 (C), R24.2
IN3P: JP3.1, OK1.5 (A), R23.1
IN4N: JP4.3, OK1.7 (C), R26.2
IN4P: JP4.1, OK1.8 (A), R25.1
IN5N: JP5.3, OK2.2 (C), R30.2
IN5P: JP5.1, OK2.1 (A), R29.1
IN6N: JP6.3, OK2.3 (C), R33.2
IN6P: JP6.1, OK2.4 (A), R32.1
IN7N: JP7.3, OK2.6 (C), R36.2
IN7P: JP7.1, OK2.5 (A), R35.1
IN8N: JP8.3, OK2.7 (C), R38.2
IN8P: JP8.1, OK2.8 (A), R37.1
IN9N: JP9.3, OK3.2 (C), R42.2
IN9P: JP9.1, OK3.1 (A), R41.1
IN10N: JP10.3, OK3.3 (C), R45.2
IN10P: JP10.1, OK3.4 (A), R44.1
IN11N: JP11.3, OK3.6 (C), R48.2
IN11P: JP11.1, OK3.5 (A), R47.1
IN12N: JP12.3, OK3.7 (C), R50.2
IN12P: JP12.1, OK3.8 (A), R49.1
unnamed: IC1.1 (OUT), IC1.2 (-IN), R2.1
unnamed: D7.3 (C1A2), IC4.3 (+IN), R57.2
unnamed: D1.3 (C1A2), IC1.3 (+IN), R1.2
unnamed: IC4.2 (-IN), IC5.4 (A4), R53.2
unnamed: IC1.6 (-IN), IC1.7 (OUT), R2.2 (1)
unnamed: D8.3 (C1A2), IC4.5 (+IN), R58.2
unnamed: D2.3 (C1A2), IC1.5 (+IN), R4.2
unnamed: IC4.6 (-IN), IC7.4 (A4), R59.2
unnamed: IC1.8 (OUT), IC1.9 (-IN), R2.3 (1)
unnamed: C21.2, IC5.6 (C6), IC6.2 (-IN), R56.1
unnamed: D3.3 (C1A2), IC1.10 (+IN), R6.2
unnamed: IC12.8 (S), R80.1
unnamed: IC1.13 (-IN), IC1.14 (OUT), R2.4 (1)
unnamed: Q1.3 (D), Q2.1 (G), R16.1
unnamed: D4.3 (C1A2), IC1.12 (+IN), R8.2
unnamed: JP13.2, R1.1, R9.1
unnamed: R58.1, R71.2, R72.2
unnamed: C32.2, IC13.8 (OSC1), X1.1
unnamed: JP18.2, R71.1
unnamed: IC4.1 (OUT), R55.1
unnamed: IC4.7 (OUT), R61.1
unnamed: JP14.2, R4.1, R10.1
unnamed: JP17.2, R73.1
unnamed: IC9.1 (X1), Y1.2
unnamed: IC5.2 (A2), R55.2
unnamed: IC7.2 (A2), R61.2
unnamed: C22.1, IC6.6 (-IN), IC7.6 (C6), R62.1
unnamed: IC8.1 (OUT), IC8.2 (-IN), R2.5 (1)
unnamed: D5.3 (C1A2), IC8.3 (+IN), R65.2
unnamed: C33.1, IC13.7 (OSC2), X1.2
unnamed: IC9.2 (X2), Y1.1
unnamed: IC8.6 (-IN), IC8.7 (OUT), R2.6 (1)
unnamed: D6.3 (C1A2), IC8.5 (+IN), R69.2
unnamed: IC12.4 (RXD), IC13.2 (RXCAN)
unnamed: BT1.PWR@1 (+), IC9.3 (VBKP)
unnamed: IC9.9 (SQW), R75.1
unnamed: IC12.1 (TXD), IC13.1 (TXCAN)
unnamed: IC9.4 (!RST), S1.2
unnamed: IC13.17 (RESET), R81.1
unnamed: C26.1, IC10.1 (IN+), R5.2
unnamed: C26.2, IC10.2 (IN-), R7.2
unnamed: C27.1, C28.2, IC10.4 (BIAS), R13.1, R14.1
unnamed: IC10.6 (ZERO_EN), IC10.9 (INT_THRS), JP21.2
OD_LAMP_AUTO_P: J13.1, JP9.2
OD_LAMP_P: J6.4, JP2.2
OIL_PRESS_SW_N: J6.5, JP1.2
OUT1: IC3.21 (GPA0), OK1.15 (COL), R19.1
OUT2: IC3.22 (GPA1), OK1.14 (COL), R22.1
OUT3: IC3.23 (GPA2), OK1.11 (COL), R27.1
OUT4: IC3.24 (GPA3), OK1.10 (COL), R28.1
OUT5: IC3.28 (GPA7), OK2.15 (COL), R31.1
OUT6: IC3.27 (GPA6), OK2.14 (COL), R34.1
OUT7: IC3.26 (GPA5), OK2.11 (COL), R39.1
OUT8: IC3.25 (GPA4), OK2.10 (COL), R40.1
OUT9: IC3.1 (GPB0), OK3.15 (COL), R43.1
OUT10: IC3.2 (GPB1), OK3.14 (COL), R46.1
OUT11: IC3.3 (GPB2), OK3.11 (COL), R51.1
OUT12: IC3.4 (GPB3), OK3.10 (COL), R52.1
PARKING_BRAKE_N: J7.2, JP11.2
SCL: IC3.12 (SCL), IC9.7 (SCL), J1.5
SDA: IC3.13 (SDA), IC9.6 (SDA), J1.3
SENSOR1_IN: J2.4, JP13.1
SENSOR2_IN: J2.3, JP14.1
SENSOR3_IN: J2.2, R6.1, R11.1
SENSOR4_IN: J2.1, R8.1, R12.1
SENSOR5_IN: J2.5, R63.1, R65.1
SENSOR6_IN: J2.6, R67.1, R69.1
SIG_3V3_IN1: C21.1, IC2.7 (CH6), IC6.1 (OUT), R56.2
SIG_3V3_IN2: C22.2, IC2.8 (CH7), IC6.7 (OUT), R62.2
SIG_12V_IN1: JP17.1
SIG_12V_IN2: JP18.1
SPI_CE0_N: J1.24, JP16.3, JP22.3
SPI_CE1_N: J1.26, JP16.1, JP22.1
SPI_CLK: IC2.13 (CLK), IC13.13 (SCK), J1.23
SPI_MISO: IC2.12 (DOUT), IC13.15 (SO), J1.21
SPI_MOSI: IC2.11 (DIN), IC13.14 (SI), J1.19
USER_IN1: IC3.5 (GPB4), J9.5, R64.2
USER_IN2: IC3.6 (GPB5), J9.2, R66.2
USER_IN3: IC3.7 (GPB6), J9.1, R68.2
USER_IN4: IC3.8 (GPB7), J9.4, R70.2
VCCA: C23.1, C25.1, IC10.10 (VCC), IC11.2 (VOUT), JP21.3, R13.2
VSS+: J11.G (VSS+), R5.1
VSS-: J11.1 (VSS-), JP15.1, R7.1

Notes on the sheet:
Resistive Sensor Inputs
12V Analog Inputs (Isolated)
Sensor/Analog Input ADC
Dash Light Inputs (Isolated)
Connect output from speedo/vss conditioning circuit to here.
RPi Header
Tach Input
RTC
GPIO Expander
Switched 12V
VSS Input Coniditioning
CAN Transceiver

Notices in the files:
parts and their libraries:
SparkFun-Jumpers: Licensing: Creative Commons ShareAlike 4.0 International - https://creativecommons.org/licenses/by-sa/4.0
